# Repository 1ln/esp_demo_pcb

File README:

Portia, Esp32 development board

Notice: Project is currently in development and has not been fully tested.

Copyright: OSHW

As an open source pcb, You choose to use at your own risk. 

You are free to use under the terms of OSHW, however if you are interested in producing this as a product it would be my preference to enjoy a royalty of any profits made and/or credit. Please don't hesitate to contact me if you are interested in producing this.

Developed by Dan Olson, 2019

This is a small, low cost development board for the ESP32 wroom module (16 GB version).

Features:

Both VSPI and HSPI have been routed to a single header.
Low noise LDO
One 3 pin rgb led for status alerts and testing.
Programming port includes a ground pin.

Please be aware that there is no usb on this board, it is meant to be programmed with an external adapter.

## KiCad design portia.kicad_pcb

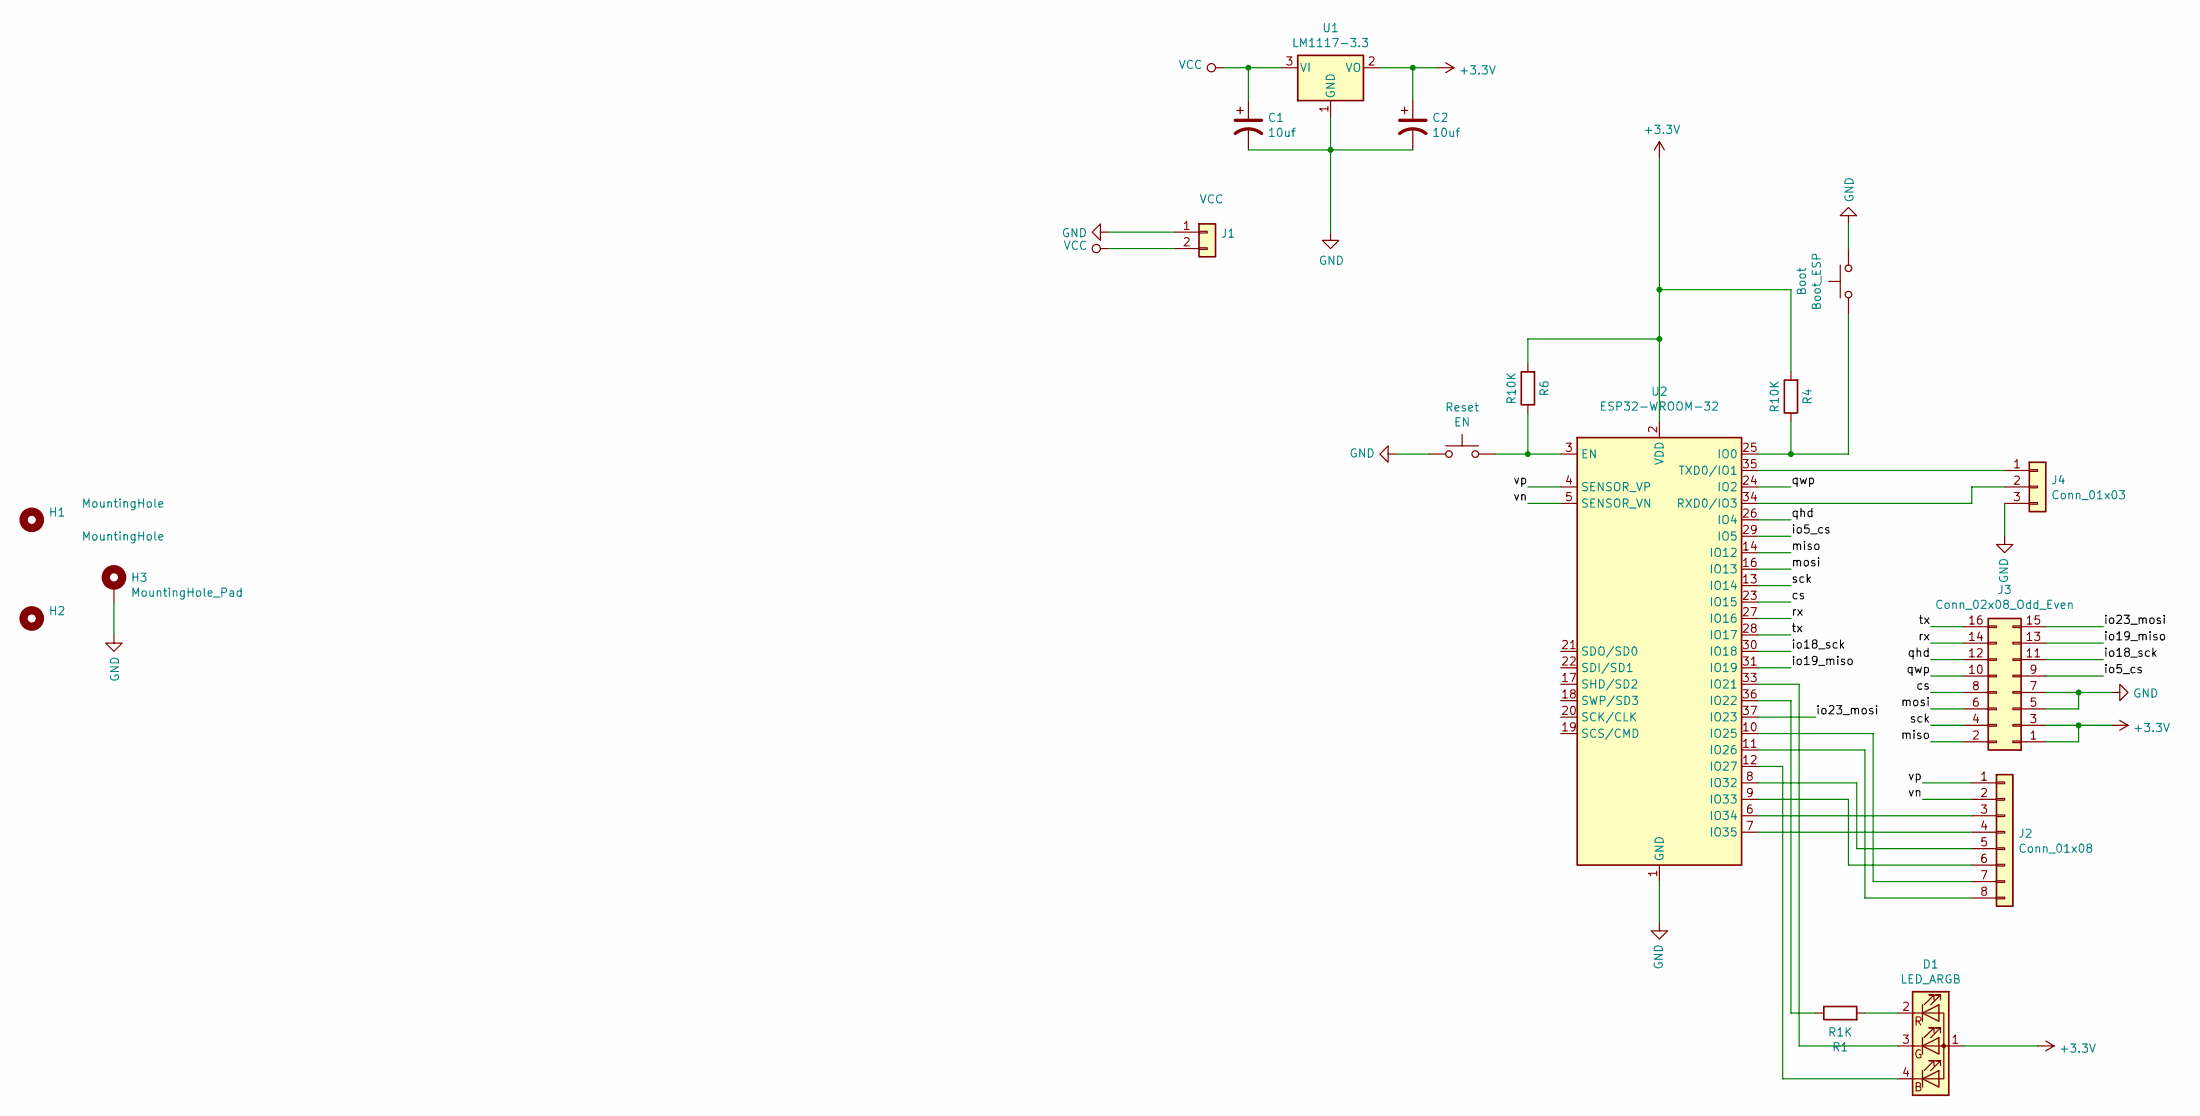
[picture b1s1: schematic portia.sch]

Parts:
Boot: Boot_ESP; SW_SPST_B3U-1000P-B
C1, C2: 10uf; C_0603_1608Metric_Pad1.05x0.95mm_HandSolder
D1: LED_ARGB; LED_RGB_5050-6
H1, H2: MountingHole; MountingHole_3mm
H3: MountingHole_Pad; MountingHole_3mm_Pad_Via
J1: VCC; PinHeader_1x02_P2.54mm_Vertical
J2: Conn_01x08; PinSocket_1x08_P2.54mm_Vertical
J3: Conn_02x08_Odd_Even; PinHeader_2x08_P2.54mm_Vertical
J4: Conn_01x03; PinHeader_1x03_P2.54mm_Vertical
R1: R1K; R_0603_1608Metric_Pad1.05x0.95mm_HandSolder
R4, R6: R10K; R_0603_1608Metric_Pad1.05x0.95mm_HandSolder
Reset: EN; SW_SPST_B3U-1000P-B
U1: LM1117-3.3; SOT-223
U2: ESP32-WROOM-32

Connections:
+3V3: C2.1, D1.1 (A), J3.1, J3.3, R4.2, R6.2, U1.2 (VO), U2.2 (VDD)
/cs: J3.8, U2.23 (IO15)
/io5_cs: J3.9, U2.29 (IO5)
/io18_sck: J3.11, U2.30 (IO18)
/io19_miso: J3.13, U2.31 (IO19)
/io23_mosi: J3.15, U2.37 (IO23)
/miso: J3.2, U2.14 (IO12)
/mosi: J3.6, U2.16 (IO13)
/qhd: J3.12, U2.26 (IO4)
/qwp: J3.10, U2.24 (IO2)
/rx: J3.14, U2.27 (IO16)
/sck: J3.4, U2.13 (IO14)
/tx: J3.16, U2.28 (IO17)
/vn: J2.2, U2.5 (SENSOR_VN)
/vp: J2.1, U2.4 (SENSOR_VP)
GND: Boot.2, C1.2, C2.2, H3.1, J1.1, J3.5, J3.7, J4.3, Reset.1, U1.1 (GND), U2.1 (GND), U2.15 (GND), U2.38 (GND)
unnamed: Boot.1, R4.1, U2.25 (IO0)
unnamed: D1.2 (RK), R1.2
unnamed: D1.3 (GK), U2.33 (IO21)
unnamed: D1.4 (BK), U2.12 (IO27)
unnamed: J2.3, U2.6 (IO34)
unnamed: J2.4, U2.7 (IO35)
unnamed: J2.5, U2.8 (IO32)
unnamed: J2.6, U2.9 (IO33)
unnamed: J2.7, U2.10 (IO25)
unnamed: J2.8, U2.11 (IO26)
unnamed: J4.1, U2.35 (TXD0/IO1)
unnamed: J4.2, U2.34 (RXD0/IO3)
unnamed: R1.1, U2.36 (IO22)
unnamed: R6.1, Reset.2, U2.3 (EN)
VCC: C1.1, J1.2, U1.3 (VI)

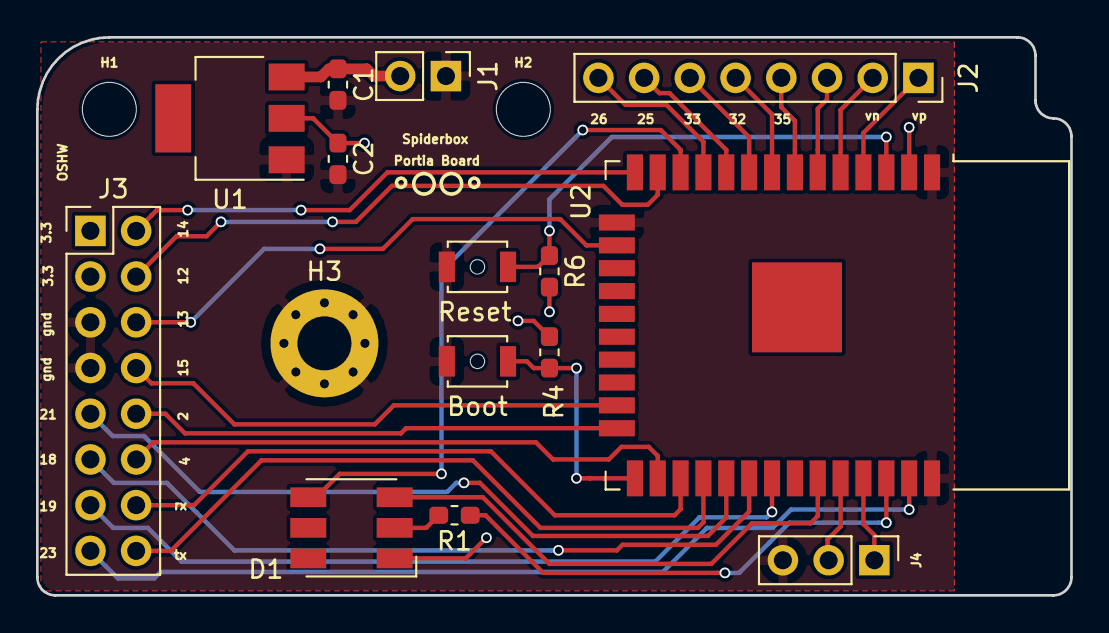
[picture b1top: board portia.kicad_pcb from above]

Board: 2 copper layers, 57.4 x 31.0 mm, 17 parts (0 on the bottom side), 31 nets.

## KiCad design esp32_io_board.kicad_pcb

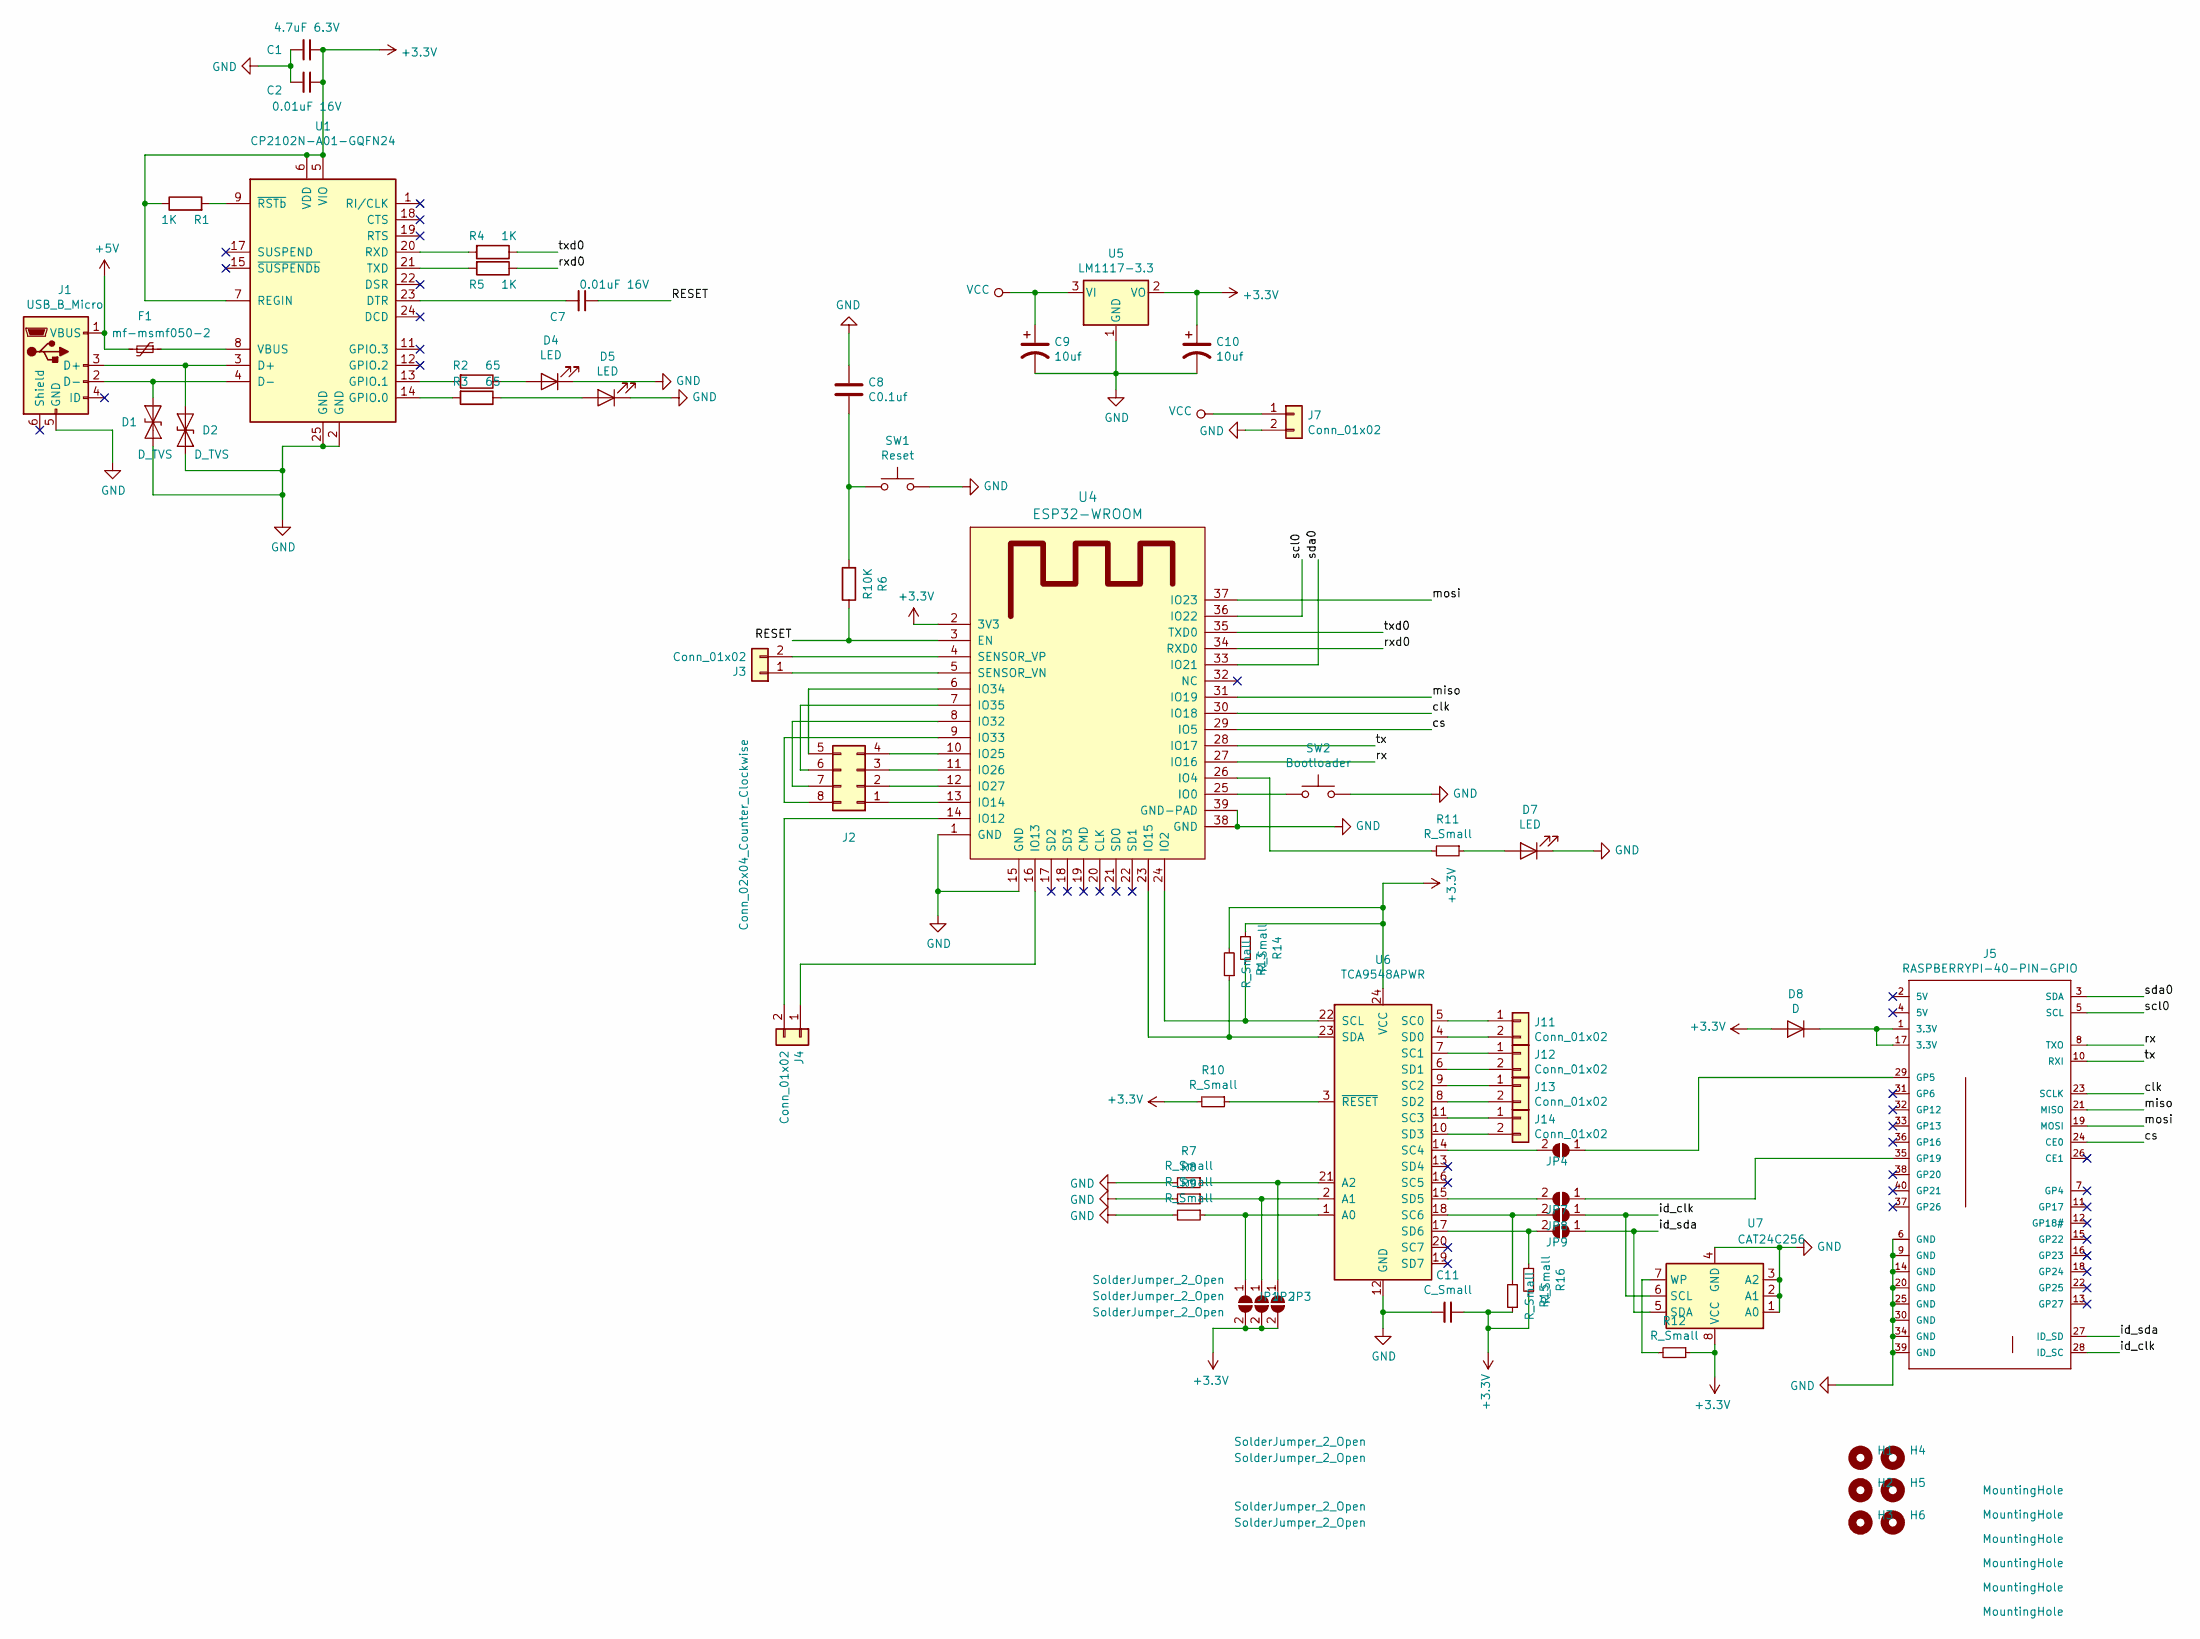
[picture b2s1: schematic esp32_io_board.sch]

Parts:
C1: 4.7uF 6.3V; C_0603_1608Metric
C2, C7: 0.01uF 16V; C_0603_1608Metric
C8: C0.1uf; C_0603_1608Metric
C9: 10uf; CP_Elec_4x5.3
C10: 10uf; CP_Elec_4x4.5
C11: C_Small; C_0603_1608Metric
D1, D2: D_TVS; D_SOD-123F
D4, D5, D7: LED; LED_0603_1608Metric
D8: D; D_SOD-123F
F1: mf-msmf050-2; Fuse_1812_4532Metric_Pad1.30x3.40mm_HandSolder
H1, H2, H3, H4, H5, H6: MountingHole; MountingHole_3mm
J1: USB_B_Micro; USB_Micro-B_Amphenol_10103594-0001LF_Horizontal
J2: Conn_02x04_Counter_Clockwise; PinHeader_2x04_P2.54mm_Vertical
J3, J4, J7, J11, J12, J13, J14: Conn_01x02; PinHeader_1x02_P2.54mm_Vertical
J5: RASPBERRYPI-40-PIN-GPIO; 2X20-SHROUDED
JP1, JP2, JP3, JP4, JP7, JP8, JP9: SolderJumper_2_Open; SolderJumper-2_P1.3mm_Open_RoundedPad1.0x1.5mm
R1, R4, R5: 1K; R_0603_1608Metric
R2, R3: 65; R_0603_1608Metric
R6: R10K; R_0603_1608Metric
R7, R8, R9, R10, R11, R12, R13, R14, R15, R16: R_Small; R_0603_1608Metric
SW1: Reset; SW_SPST_EVPBF
SW2: Bootloader; SW_SPST_EVPBF
U1: CP2102N-A01-GQFN24; QFN-24-1EP_4x4mm_P0.5mm_EP2.6x2.6mm
U4: ESP32-WROOM
U5: LM1117-3.3; SOT-223
U6: TCA9548APWR; TSSOP-24_4.4x7.8mm_P0.65mm
U7: CAT24C256; SOIC-8-1EP_3.9x4.9mm_P1.27mm_EP2.35x2.35mm

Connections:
+3V3: C1.1, C2.1, C10.1, C11.1, D8.2 (A), JP1.2 (B), JP2.2 (B), JP3.2 (B), R1.1, R10.2, R12.1, R13.2, R14.2, R15.1, R16.1, U1.5 (VIO), U1.6 (VDD), U1.7 (REGIN), U4.2 (3V3), U5.2 (VO), U6.24 (VCC), U7.8 (VCC)
+5V: F1.2, J1.1 (VBUS)
/RESET: C7.1, R6.1, U4.3 (EN)
/clk: J5.23 (SCLK), U4.30 (IO18)
/cs: J5.24 (CE0), U4.29 (IO5)
/id_clk: J5.28 (ID_SC), JP8.1 (A), U7.6 (SCL)
/id_sda: J5.27 (ID_SD), JP9.1 (A), U7.5 (SDA)
/miso: J5.21 (MISO), U4.31 (IO19)
/mosi: J5.19 (MOSI), U4.37 (IO23)
/rx: J5.8 (TXO), U4.27 (IO16)
/rxd0: R5.1, U4.34 (RXD0)
/scl0: J5.5 (SCL), U4.36 (IO22)
/sda0: J5.3 (SDA), U4.33 (IO21)
/tx: J5.10 (RXI), U4.28 (IO17)
/txd0: R4.1, U4.35 (TXD0)
GND: C1.2, C2.2, C8.1, C9.2, C10.2, C11.2, D1.2 (A2), D2.2 (A2), D4.1 (K), D5.1 (K), D7.1 (K), J1.5 (GND), J5.6 (GND), J5.9 (GND), J5.14 (GND), J5.20 (GND), J5.25 (GND), J5.30 (GND), J5.34 (GND), J5.39 (GND), J7.2, R7.2, R8.2, R9.2, SW1.2, SW2.2, U1.2 (GND), U1.25 (GND), U4.1 (GND), U4.15 (GND), U4.38 (GND), U4.39 (GND-PAD), U5.1 (GND), U6.12 (GND), U7.1 (A0), U7.2 (A1), U7.3 (A2), U7.4 (GND)
unnamed: C7.2, U1.23 (DTR)
unnamed: C8.2, R6.2, SW1.1
unnamed: D1.1 (A1), J1.2 (D-), U1.4 (D-)
unnamed: D2.1 (A1), J1.3 (D+), U1.3 (D+)
unnamed: D4.2 (A), R2.1
unnamed: D5.2 (A), R3.1
unnamed: D7.2 (A), R11.1
unnamed: D8.1 (K), J5.1 (3.3V), J5.17 (3.3V)
unnamed: F1.1, U1.8 (VBUS)
unnamed: J2.1, U4.13 (IO14)
unnamed: J2.2, U4.12 (IO27)
unnamed: J2.3, U4.11 (IO26)
unnamed: J2.4, U4.10 (IO25)
unnamed: J2.5, U4.6 (IO34)
unnamed: J2.6, U4.7 (IO35)
unnamed: J2.7, U4.8 (IO32)
unnamed: J2.8, U4.9 (IO33)
unnamed: J3.1, U4.5 (SENSOR_VN)
unnamed: J3.2, U4.4 (SENSOR_VP)
unnamed: J4.1, U4.16 (IO13)
unnamed: J4.2, U4.14 (IO12)
unnamed: J5.29 (GP5), JP4.1 (A)
unnamed: J5.35 (GP19), JP7.1 (A)
unnamed: J11.1, U6.5 (SC0)
unnamed: J11.2, U6.4 (SD0)
unnamed: J12.1, U6.7 (SC1)
unnamed: J12.2, U6.6 (SD1)
unnamed: J13.1, U6.9 (SC2)
unnamed: J13.2, U6.8 (SD2)
unnamed: J14.1, U6.11 (SC3)
unnamed: J14.2, U6.10 (SD3)
unnamed: JP1.1 (A), R9.1, U6.1 (A0)
unnamed: JP2.1 (A), R8.1, U6.2 (A1)
unnamed: JP3.1 (A), R7.1, U6.21 (A2)
unnamed: JP4.2 (B), U6.14 (SC4)
unnamed: JP7.2 (B), U6.15 (SD5)
unnamed: JP8.2 (B), R15.2, U6.18 (SC6)
unnamed: JP9.2 (B), R16.2, U6.17 (SD6)
unnamed: R1.2, U1.9 (~RSTb)
unnamed: R2.2, U1.13 (GPIO.1)
unnamed: R3.2, U1.14 (GPIO.0)
unnamed: R4.2, U1.20 (RXD)
unnamed: R5.2, U1.21 (TXD)
unnamed: R10.1, U6.3 (~RESET)
unnamed: R11.2, U4.26 (IO4)
unnamed: R12.2, U7.7 (WP)
unnamed: R13.1, U4.23 (IO15), U6.23 (SDA)
unnamed: R14.1, U4.24 (IO2), U6.22 (SCL)
unnamed: SW2.1, U4.25 (IO0)
VCC: C9.1, J7.1, U5.3 (VI)

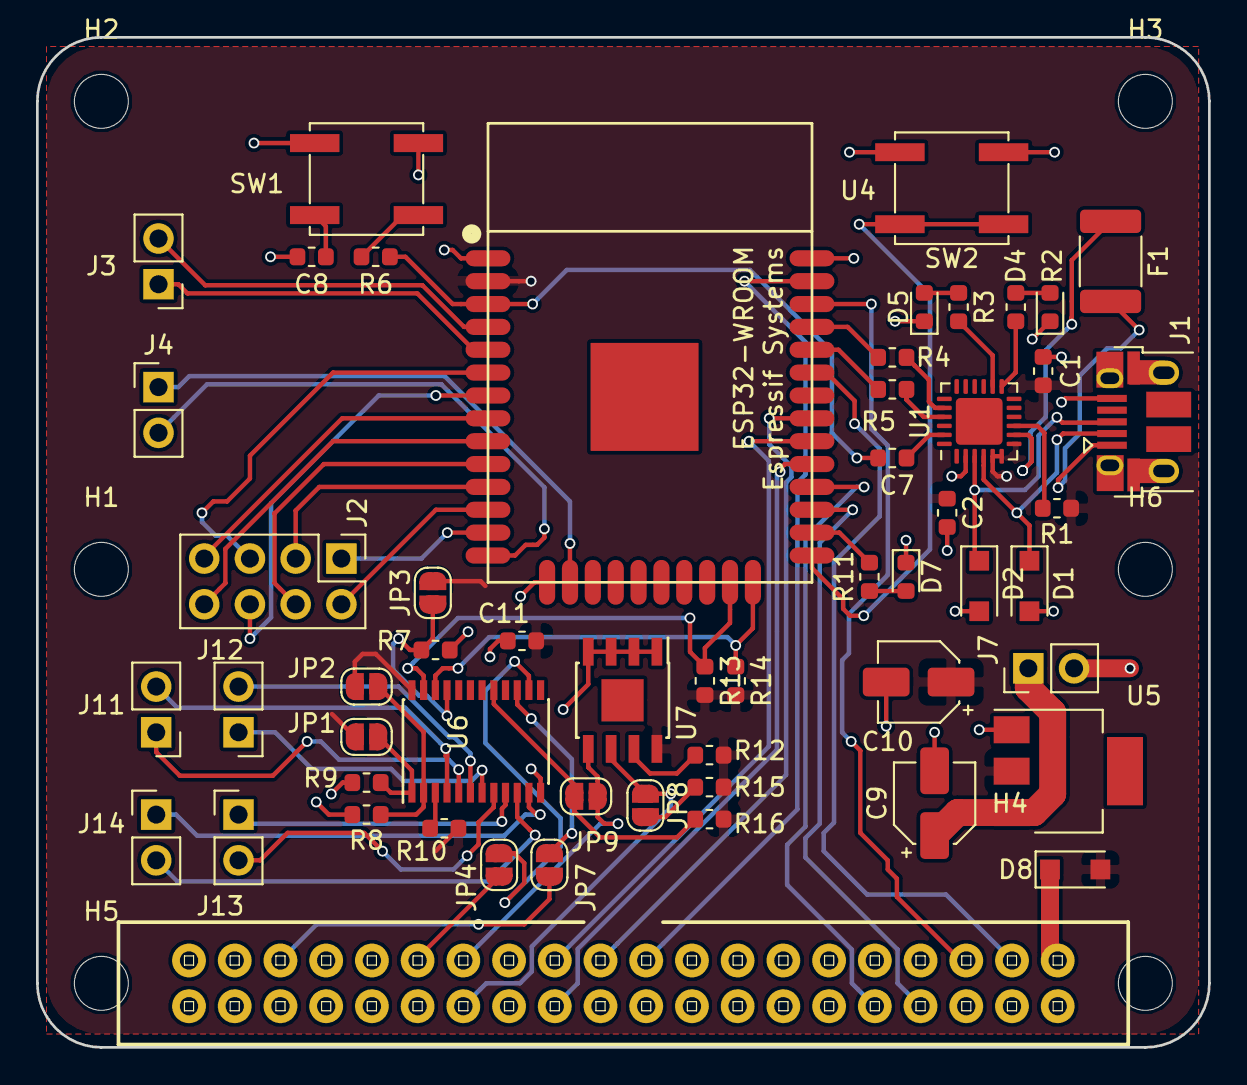
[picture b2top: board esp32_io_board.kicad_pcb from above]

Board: 2 copper layers, 65.1 x 56.1 mm, 60 parts (0 on the bottom side), 66 nets.

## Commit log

2018-11-13 inital commit
2018-11-15 schematic
2018-11-29 usb bus cp1202n
2018-12-16 removed 3 sx1509 chips
2018-12-18 modified design
2018-12-18 generate pdf
2018-12-21 rgb addressable led indication
2018-12-21 tca9548
2018-12-22 spi ports
2018-12-22 final schematic
2018-12-22 reset on dtr
2018-12-22 power pins added on txb104
2018-12-22 cvpcb
2018-12-22 initial netlist
2018-12-22 initial import
2018-12-22 initial layout without traces
2018-12-23 redesign
2018-12-23 annotation
2018-12-24 raspberry pi integration
2018-12-25 i2c jumpers
2018-12-25 layout
2018-12-26 layout update
2018-12-26 layout design
2018-12-29 pcb final layout adjustments
2018-12-29 readme
2018-12-30 portia
2018-12-30 modified todo
2019-01-02 modified trace connections
2019-01-02 resolved routing issue
2019-01-03 redesign removed 40 pin header
2019-01-04 redesigned i2c bus
2019-01-04 removed extra trace
2019-01-04 updated schematic redesign
2019-01-05 adding new layout components
2019-01-05 redesign layout sensors
2019-01-06 ground plane fill
2019-01-06 gerber
2019-01-06 updated png
2019-01-07 added ground ports
2019-01-10 fix i2c net list +3V3
2019-01-10 add unconnected ground esp32
2019-01-12 modify reference designators
2019-01-12 modify pad properties
2019-01-12 add name of board
2019-01-12 add ground
2019-01-12 board design complete
2019-01-12 modify silkscreen
2019-01-24 update redesign add esp32
2019-01-24 update esp32 samd51 redesign
2019-01-26 add power schematic samd51d
2019-01-26 add transient tvs usb
2019-01-26 update layout
2019-01-27 add initial schematic
2019-01-27 removed esd
2019-02-23 update schematic
2019-02-25 layout redesign
2019-02-27 add castellated footprint
2019-03-07 add traces
2019-03-25 update gerber
2019-03-26 update design
2019-03-28 update latest
2019-05-22 update redesign
2019-05-27 update pcb
